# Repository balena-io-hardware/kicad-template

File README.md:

# KiCAD v5 Example Project

## Description

This is an example KiCAD v5 project.

## Notes

This repo can be used as a template for new KiCAD v5 projects. 
For ease of getting started, click `Use this template` in the top right of the repo page; this will duplicate this repo for you to edit.
Please retain the directory structure and naming conventions.

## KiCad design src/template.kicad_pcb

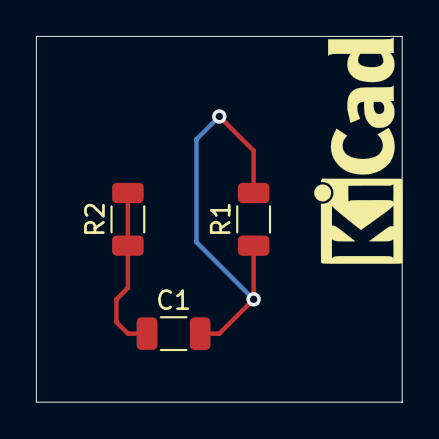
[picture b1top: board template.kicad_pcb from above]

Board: 2 copper layers, 20.3 x 20.3 mm, 4 parts (0 on the bottom side), 2 nets.

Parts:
C1: C; C_1206_3216Metric
LOGO1: Logo_Open_Hardware_Large; KiCad-Logo_5mm_SilkScreen
R1, R2: 100; R_1206_3216Metric

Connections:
unnamed: C1.1, R2.1, R2.2
unnamed: C1.2, R1.1, R1.2

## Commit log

2021-01-13 Initial release of KiCAD v5 template
    Change-type: major
